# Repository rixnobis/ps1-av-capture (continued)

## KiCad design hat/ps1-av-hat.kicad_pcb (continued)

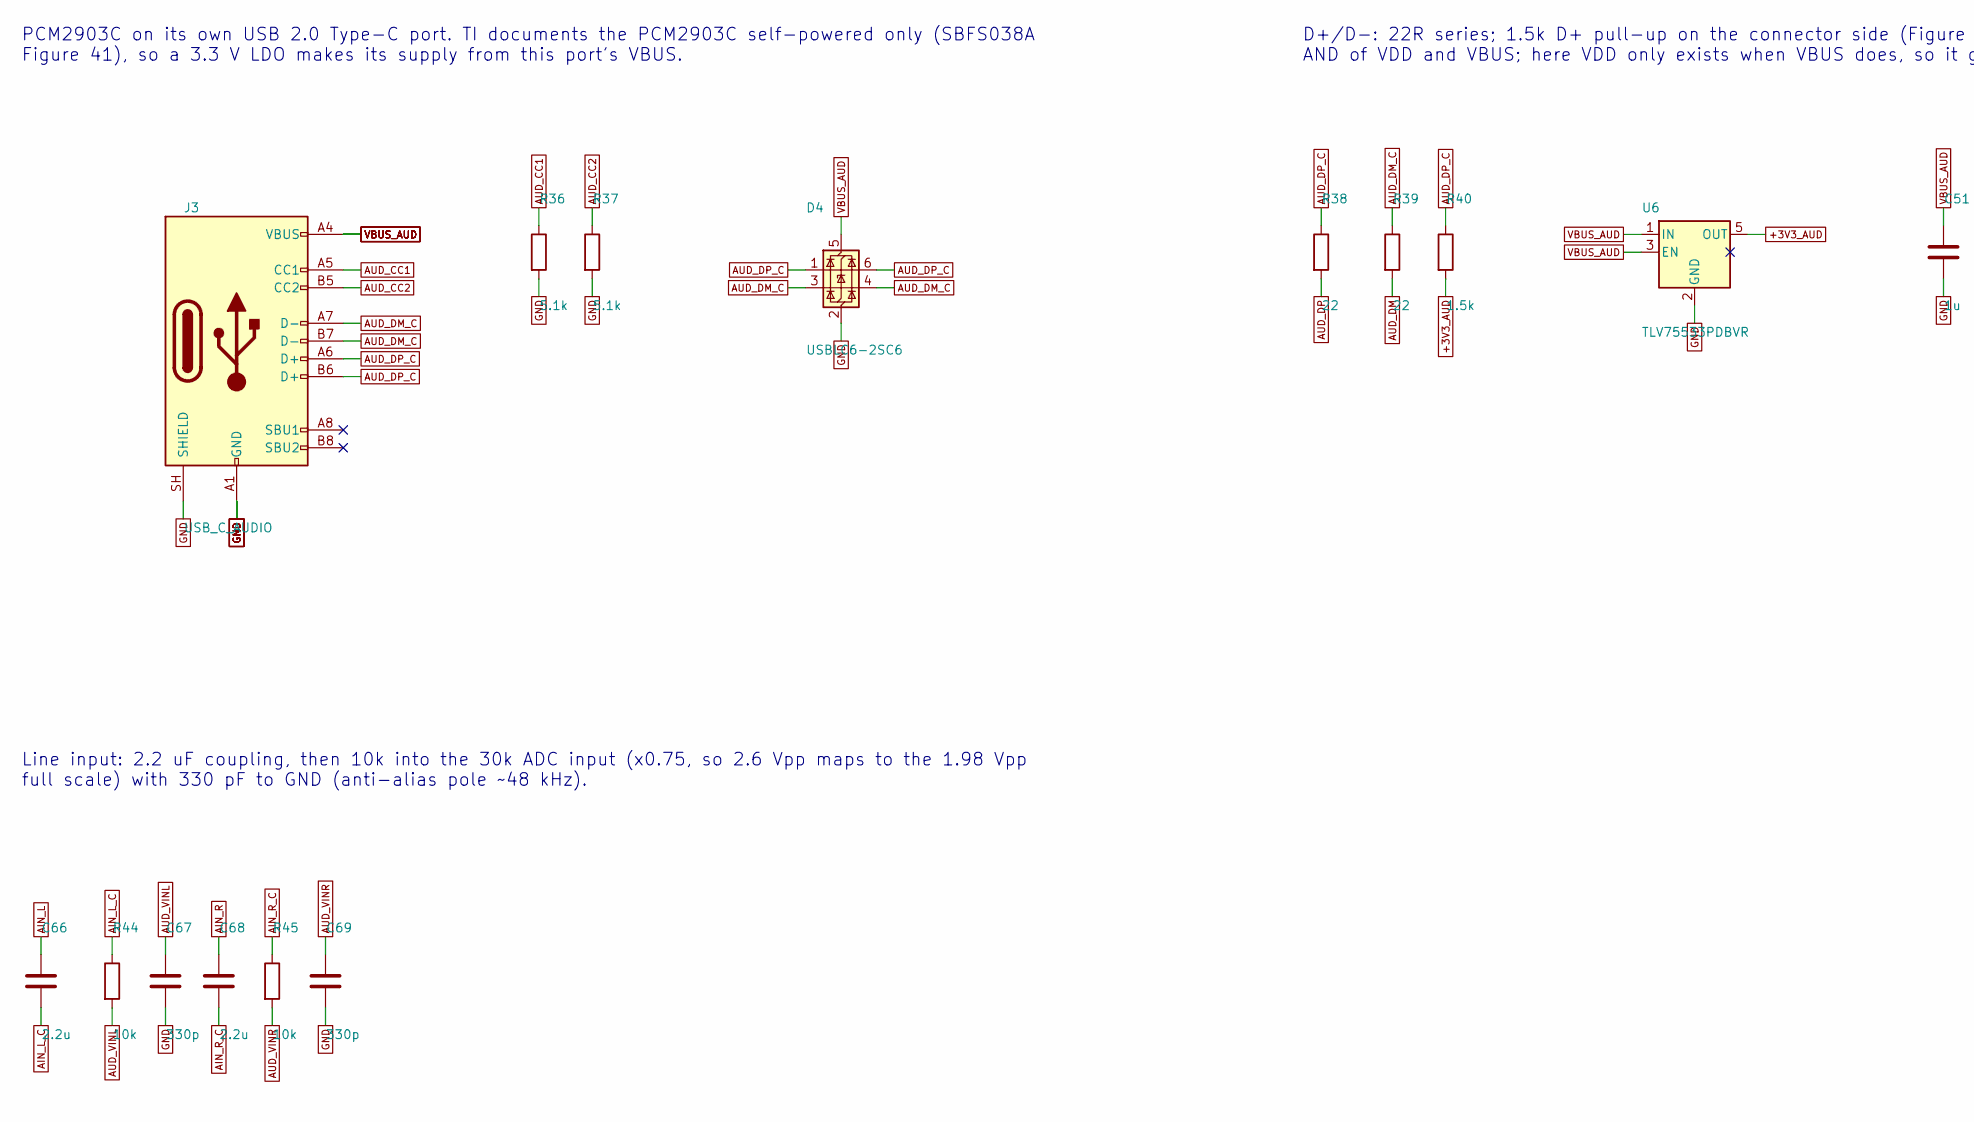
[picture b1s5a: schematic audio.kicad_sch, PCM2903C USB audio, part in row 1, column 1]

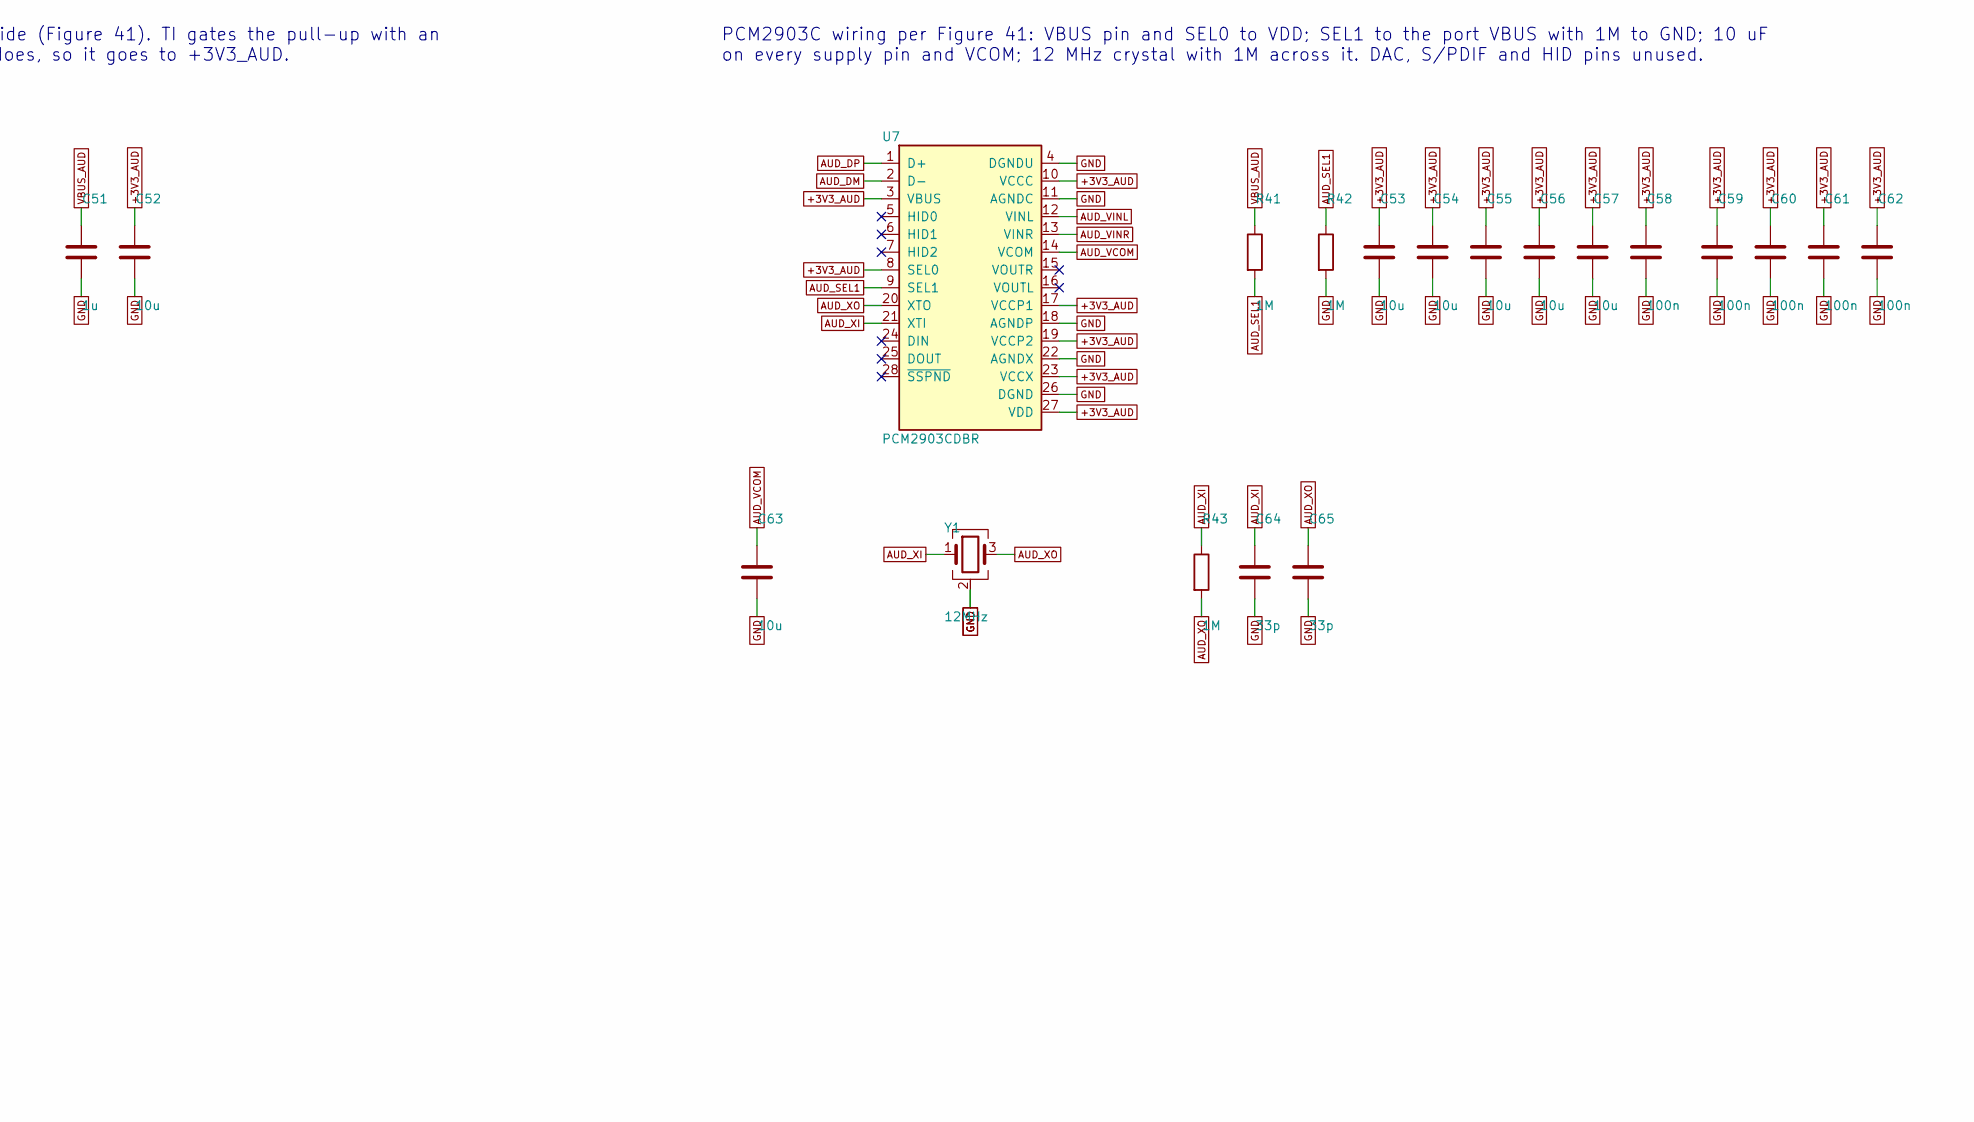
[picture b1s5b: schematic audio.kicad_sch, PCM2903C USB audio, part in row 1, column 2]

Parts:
C51: 1u; C_0402_1005Metric; LCSC C52923
C52, C53, C54, C55, C56, C57, C63: 10u; C_0603_1608Metric; LCSC C19702
C58, C59, C60, C61, C62: 100n; C_0402_1005Metric; LCSC C1525
C64, C65: 33p; C_0402_1005Metric; LCSC C1562
C66, C68: 2.2u; C_0603_1608Metric; LCSC C23630
C67, C69: 330p; C_0402_1005Metric; LCSC C13533
D4: USBLC6-2SC6; SOT-23-6; LCSC C7519
J3: USB_C_AUDIO; USB_C_Receptacle_HRO_TYPE-C-31-M-12; LCSC C165948
R36, R37: 5.1k; R_0402_1005Metric; LCSC C25905
R38, R39: 22; R_0402_1005Metric; LCSC C25092
R40: 1.5k; R_0402_1005Metric; LCSC C25867
R41, R42, R43: 1M; R_0402_1005Metric; LCSC C26083
R44, R45: 10k; R_0402_1005Metric; LCSC C25744
U6: TLV75533PDBVR; SOT-23-5; LCSC C404027
U7: PCM2903CDBR; SSOP-28_5.3x10.2mm_P0.65mm; LCSC C2861593
Y1: 12MHz; Crystal_SMD_3225-4Pin_3.2x2.5mm; LCSC C9002

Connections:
+3V3_AUD: C52.1, C53.1, C54.1, C55.1, C56.1, C57.1, C58.1, C59.1, C60.1, C61.1, C62.1, R40.2, U6.5 (OUT), U7.3 (VBUS), U7.8 (SEL0), U7.10 (VCCC), U7.17 (VCCP1), U7.19 (VCCP2), U7.23 (VCCX), U7.27 (VDD)
AIN_L: C66.1; also elsewhere on the board
AIN_L_C: C66.2, R44.1; also elsewhere on the board
AIN_R: C68.1; also elsewhere on the board
AIN_R_C: C68.2, R45.1; also elsewhere on the board
AUD_CC1: J3.A5 (CC1), R36.1
AUD_CC2: J3.B5 (CC2), R37.1
AUD_DM: R39.2, U7.2 (D-)
AUD_DM_C: D4.3 (I/O2), D4.4 (I/O2), J3.A7 (D-), J3.B7 (D-), R39.1
AUD_DP: R38.2, U7.1 (D+)
AUD_DP_C: D4.1 (I/O1), D4.6 (I/O1), J3.A6 (D+), J3.B6 (D+), R38.1, R40.1
AUD_SEL1: R41.2, R42.1, U7.9 (SEL1)
AUD_VCOM: C63.1, U7.14 (VCOM)
AUD_VINL: C67.1, R44.2, U7.12 (VINL)
AUD_VINR: C69.1, R45.2, U7.13 (VINR)
AUD_XI: C64.1, R43.1, U7.21 (XTI), Y1.1
AUD_XO: C65.1, R43.2, U7.20 (XTO), Y1.3
GND: C51.2, C52.2, C53.2, C54.2, C55.2, C56.2, C57.2, C58.2, C59.2, C60.2, C61.2, C62.2, C63.2, C64.2, C65.2, C67.2, C69.2, D4.2 (GND), J3.A1 (GND), J3.A12 (GND), J3.B1 (GND), J3.B12 (GND), J3.SH (SHIELD), R36.2, R37.2, R42.2, U6.2 (GND), U7.4 (DGNDU), U7.11 (AGNDC), U7.18 (AGNDP), U7.22 (AGNDX), U7.26 (DGND), Y1.2 (G), Y1.4 (G); also elsewhere on the board
VBUS_AUD: C51.1, D4.5 (VBUS), J3.A4 (VBUS), J3.A9 (VBUS), J3.B4 (VBUS), J3.B9 (VBUS), R41.1, U6.1 (IN), U6.3 (EN)

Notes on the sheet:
PCM2903C on its own USB 2.0 Type-C port. TI documents the PCM2903C self-powered only (SBFS038A Figure 41), so a 3.3 V LDO makes its supply from this port's VBUS.
D+/D-: 22R series; 1.5k D+ pull-up on the connector side (Figure 41). TI gates the pull-up with an AND of VDD and VBUS; here VDD only exists when VBUS does, so it goes to +3V3_AUD.
PCM2903C wiring per Figure 41: VBUS pin and SEL0 to VDD; SEL1 to the port VBUS with 1M to GND; 10 uF on every supply pin and VCOM; 12 MHz crystal with 1M across it. DAC, S/PDIF and HID pins unused.
Line input: 2.2 uF coupling, then 10k into the 30k ADC input (x0.75, so 2.6 Vpp maps to the 1.98 Vpp full scale) with 330 pF to GND (anti-alias pole ~48 kHz).

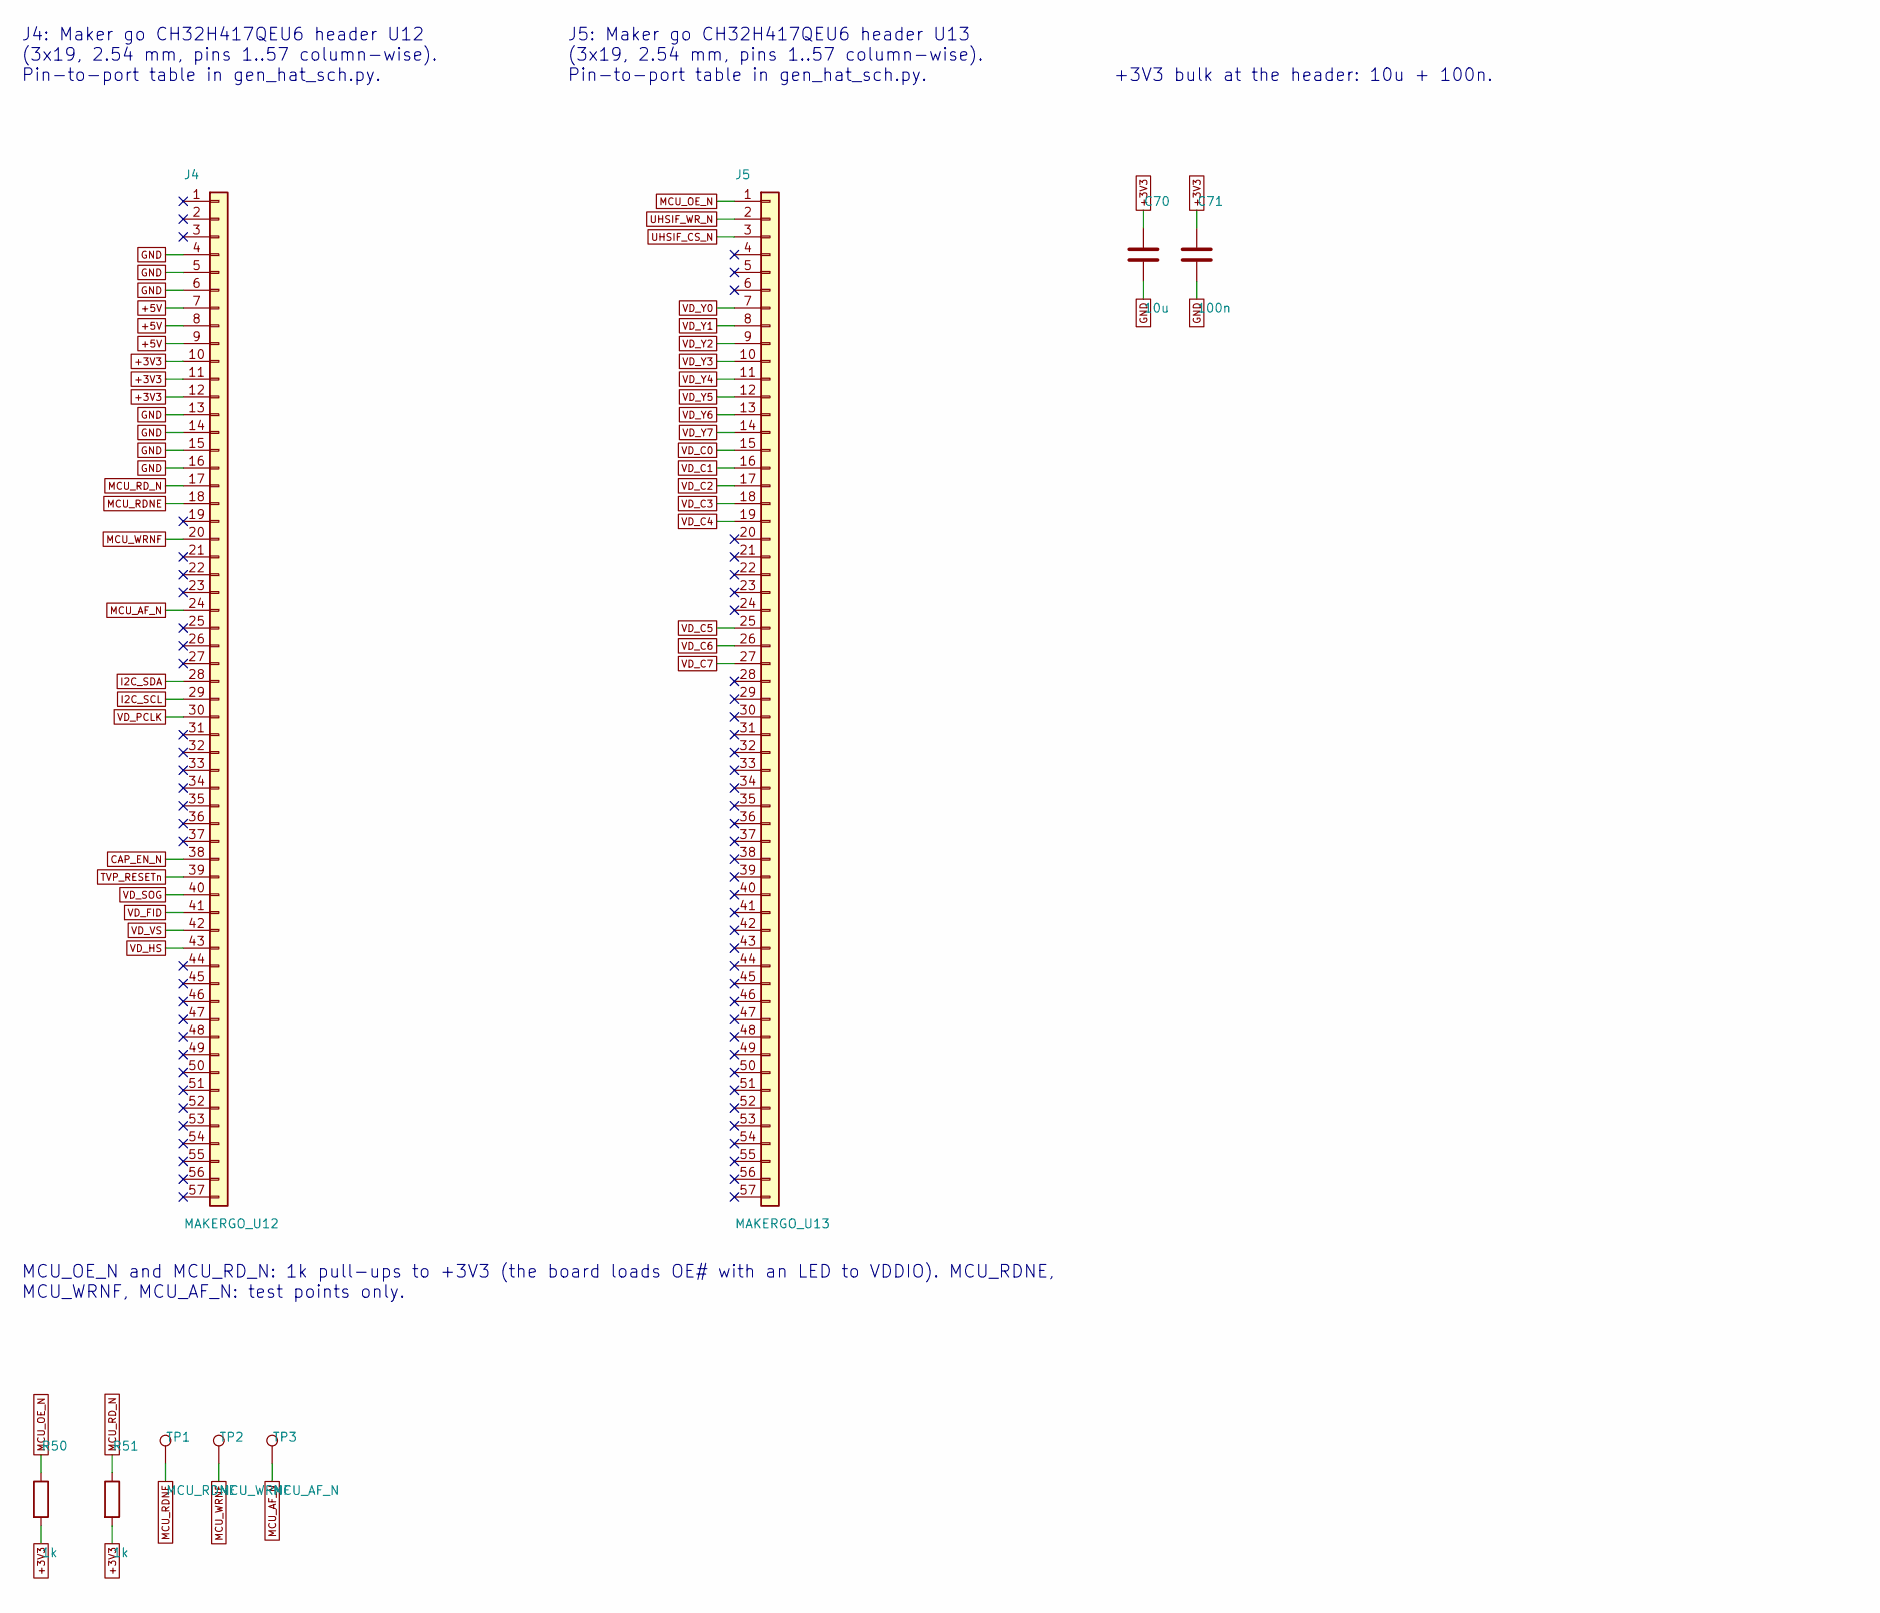
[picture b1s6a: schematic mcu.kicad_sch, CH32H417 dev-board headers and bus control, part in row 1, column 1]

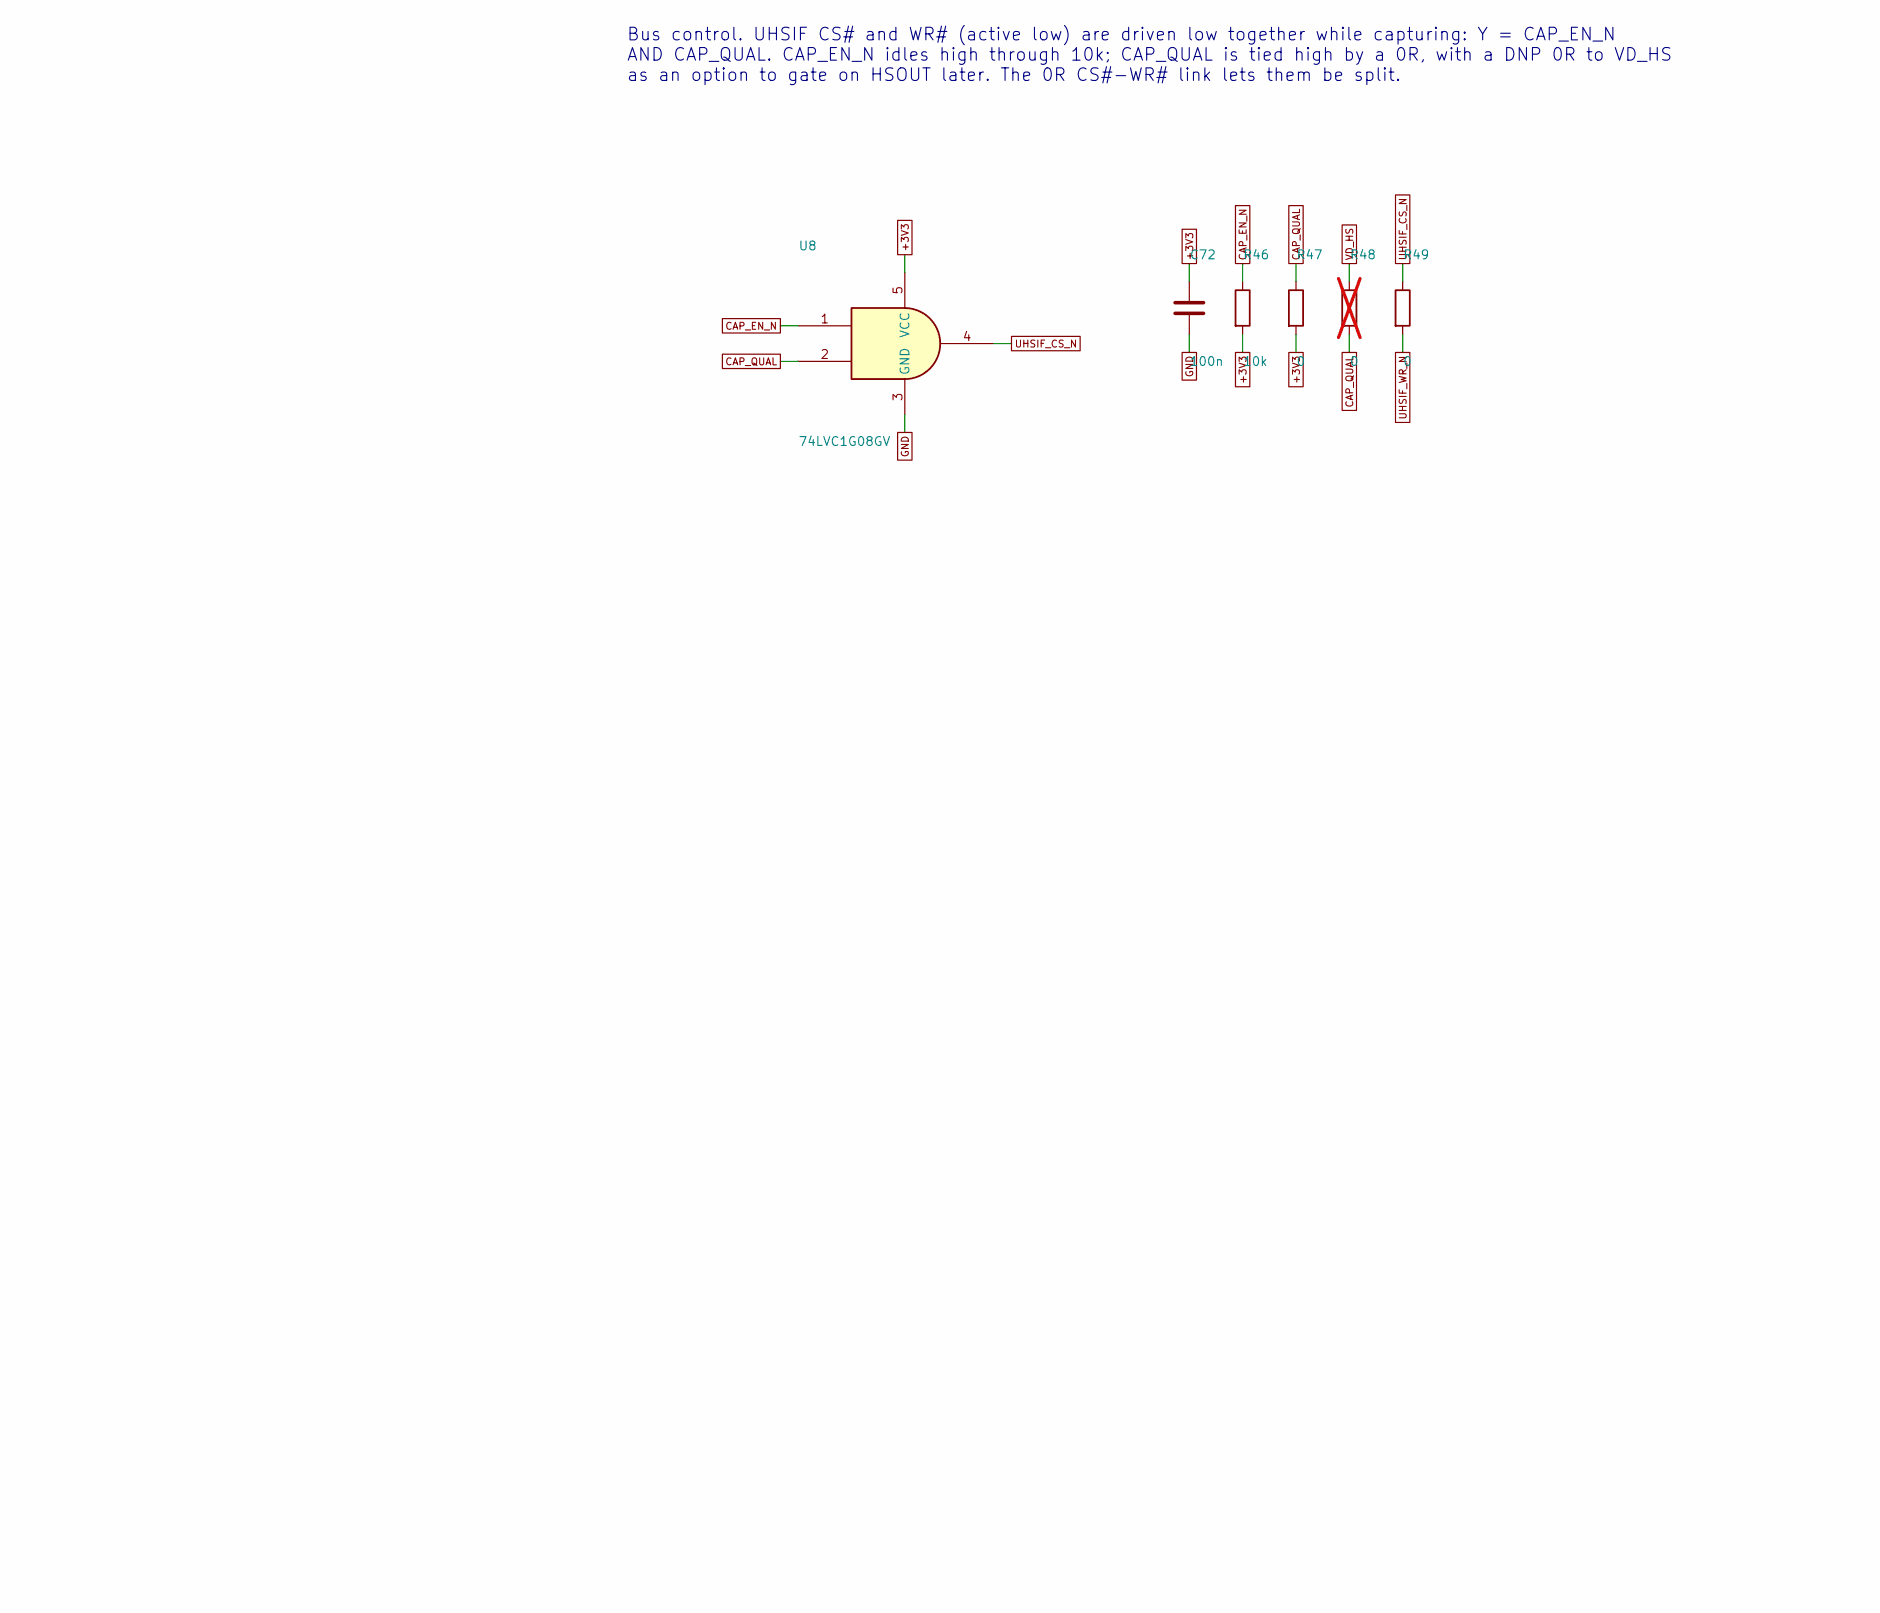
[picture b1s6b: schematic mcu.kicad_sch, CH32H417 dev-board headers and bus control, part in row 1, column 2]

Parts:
C70: 10u; C_0603_1608Metric; LCSC C19702
C71, C72: 100n; C_0402_1005Metric; LCSC C1525
J4: MAKERGO_U12; Socket_3x19_P2.54_MakerGo
J5: MAKERGO_U13; Socket_3x19_P2.54_MakerGo
R46: 10k; R_0402_1005Metric; LCSC C25744
R47, R49: 0; R_0402_1005Metric; LCSC C17168
R48: 0; R_0402_1005Metric; LCSC C17168; not fitted
R50, R51: 1k; R_0402_1005Metric; LCSC C11702
TP1: MCU_RDNE; TestPoint_Pad_D1.0mm
TP2: MCU_WRNF; TestPoint_Pad_D1.0mm
TP3: MCU_AF_N; TestPoint_Pad_D1.0mm
U8: 74LVC1G08GV; SOT-23-5; LCSC C19829591

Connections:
+3V3: C70.1, C71.1, C72.1, J4.10, J4.11, J4.12, R46.2, R47.2, R50.2, R51.2, U8.5 (VCC); also elsewhere on the board
+5V: J4.7, J4.8, J4.9; also elsewhere on the board
CAP_EN_N: J4.38, R46.1, U8.1
CAP_QUAL: R47.1, R48.2, U8.2
GND: C70.2, C71.2, C72.2, J4.4, J4.5, J4.6, J4.13, J4.14, J4.15, J4.16, U8.3 (GND); also elsewhere on the board
I2C_SCL: J4.29; also elsewhere on the board
I2C_SDA: J4.28; also elsewhere on the board
MCU_AF_N: J4.24, TP3.1
MCU_OE_N: J5.1, R50.1
MCU_RDNE: J4.18, TP1.1
MCU_RD_N: J4.17, R51.1
MCU_WRNF: J4.20, TP2.1
TVP_RESETn: J4.39; also elsewhere on the board
UHSIF_CS_N: J5.3, R49.1, U8.4
UHSIF_WR_N: J5.2, R49.2
VD_C0: J5.15; also elsewhere on the board
VD_C1: J5.16; also elsewhere on the board
VD_C2: J5.17; also elsewhere on the board
VD_C3: J5.18; also elsewhere on the board
VD_C4: J5.19; also elsewhere on the board
VD_C5: J5.25; also elsewhere on the board
VD_C6: J5.26; also elsewhere on the board
VD_C7: J5.27; also elsewhere on the board
VD_FID: J4.41; also elsewhere on the board
VD_HS: J4.43, R48.1; also elsewhere on the board
VD_PCLK: J4.30; also elsewhere on the board
VD_SOG: J4.40; also elsewhere on the board
VD_VS: J4.42; also elsewhere on the board
VD_Y0: J5.7; also elsewhere on the board
VD_Y1: J5.8; also elsewhere on the board
VD_Y2: J5.9; also elsewhere on the board
VD_Y3: J5.10; also elsewhere on the board
VD_Y4: J5.11; also elsewhere on the board
VD_Y5: J5.12; also elsewhere on the board
VD_Y6: J5.13; also elsewhere on the board
VD_Y7: J5.14; also elsewhere on the board

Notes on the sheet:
J4: Maker go CH32H417QEU6 header U12 (3x19, 2.54 mm, pins 1..57 column-wise). Pin-to-port table in gen_hat_sch.py.
J5: Maker go CH32H417QEU6 header U13 (3x19, 2.54 mm, pins 1..57 column-wise). Pin-to-port table in gen_hat_sch.py.
+3V3 bulk at the header: 10u + 100n.
Bus control. UHSIF CS# and WR# (active low) are driven low together while capturing: Y = CAP_EN_N AND CAP_QUAL. CAP_EN_N idles high through 10k; CAP_QUAL is tied high by a 0R, with a DNP 0R to VD_HS as an option to gate on HSOUT later. The 0R CS#-WR# link lets them be split.
MCU_OE_N and MCU_RD_N: 1k pull-ups to +3V3 (the board loads OE# with an LED to VDDIO). MCU_RDNE, MCU_WRNF, MCU_AF_N: test points only.

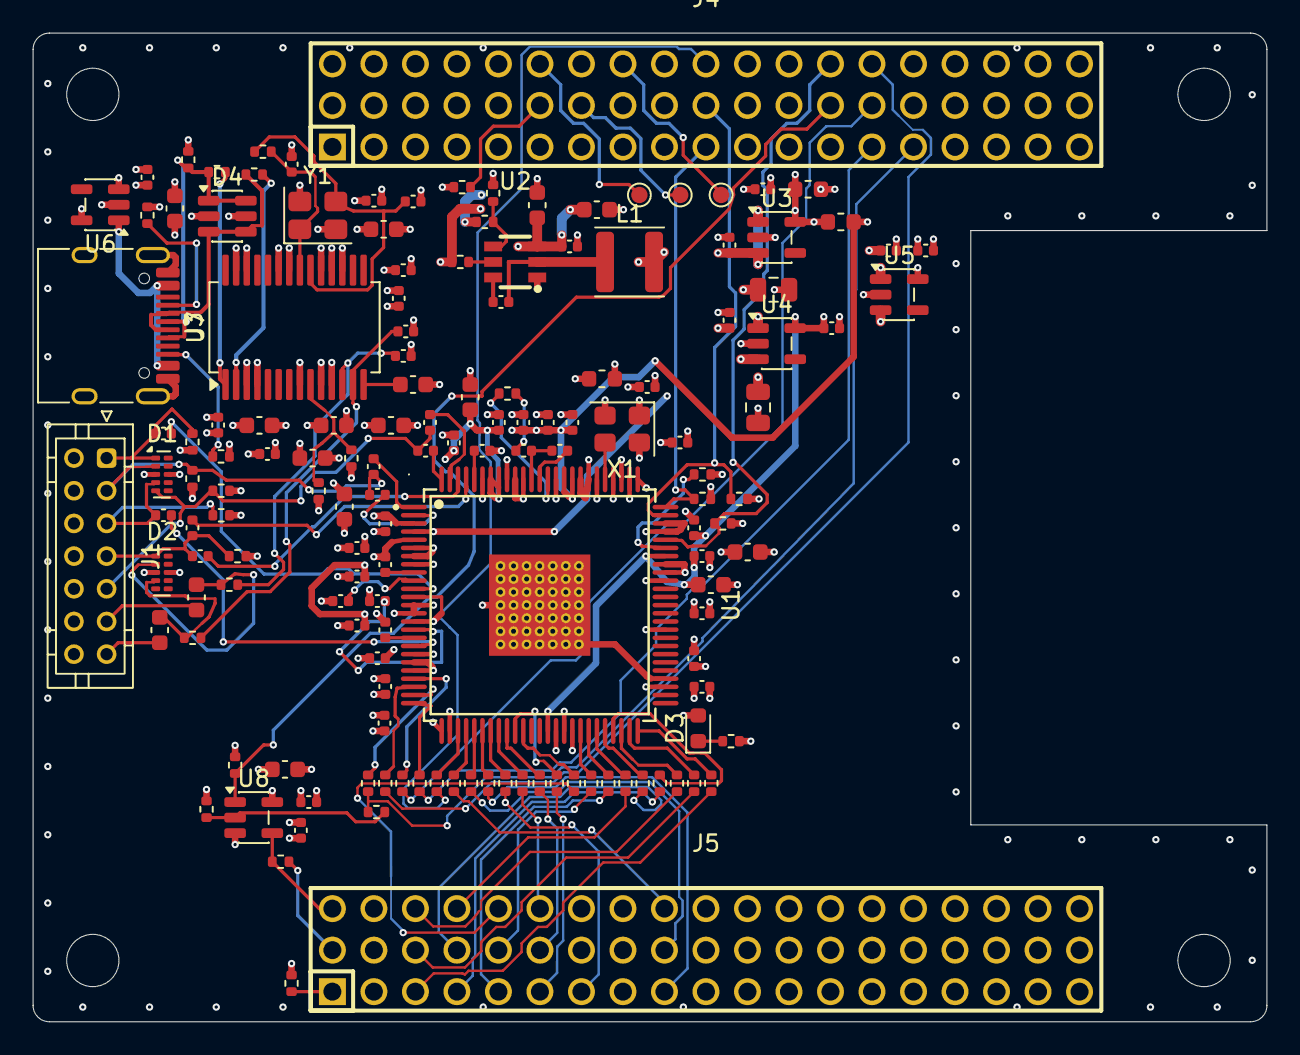
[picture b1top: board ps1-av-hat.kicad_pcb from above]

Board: 4 copper layers, 75.5 x 60.5 mm, 152 parts (0 on the bottom side), 111 nets.

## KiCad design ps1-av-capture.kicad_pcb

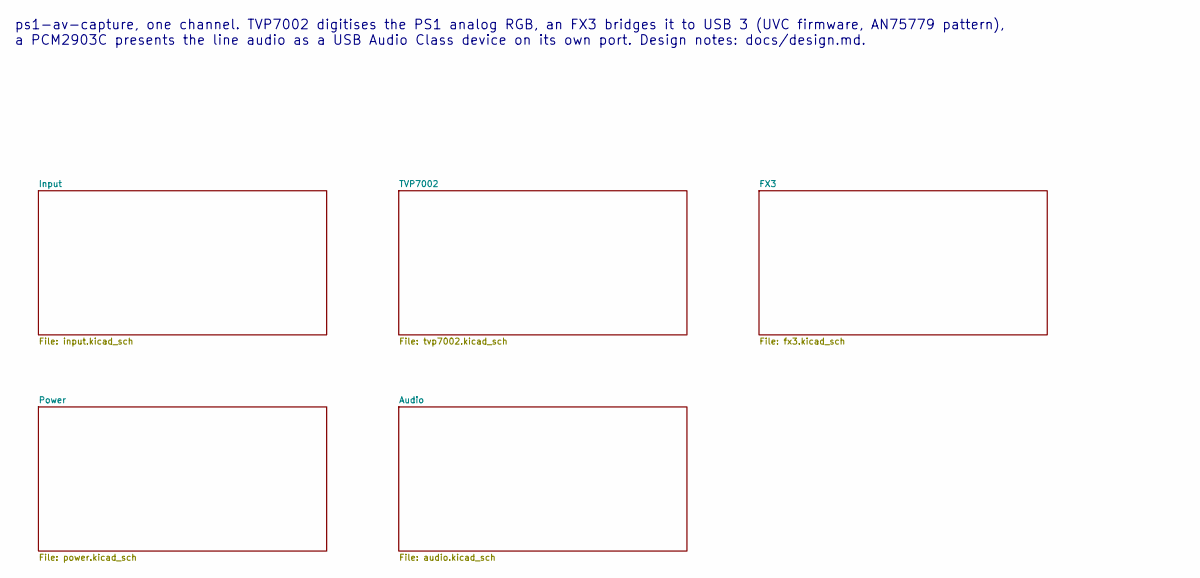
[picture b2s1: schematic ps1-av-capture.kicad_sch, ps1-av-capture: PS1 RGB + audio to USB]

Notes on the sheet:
ps1-av-capture, one channel. TVP7002 digitises the PS1 analog RGB, an FX3 bridges it to USB 3 (UVC firmware, AN75779 pattern), a PCM2903C presents the line audio as a USB Audio Class device on its own port. Design notes: docs/design.md.

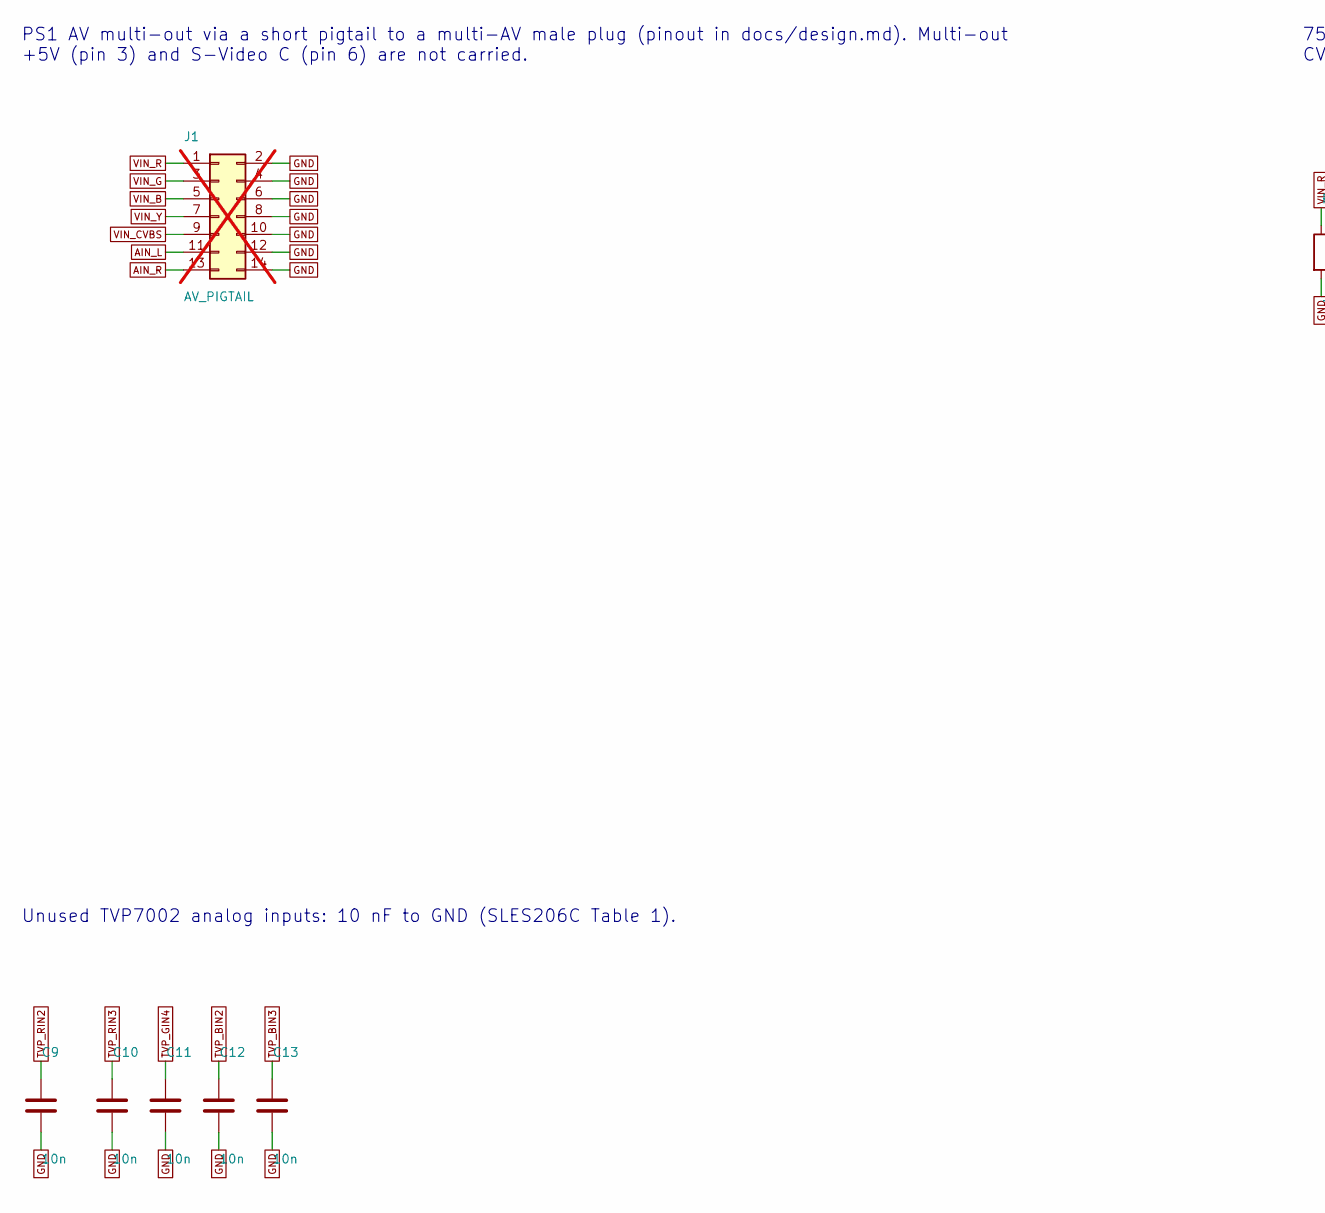
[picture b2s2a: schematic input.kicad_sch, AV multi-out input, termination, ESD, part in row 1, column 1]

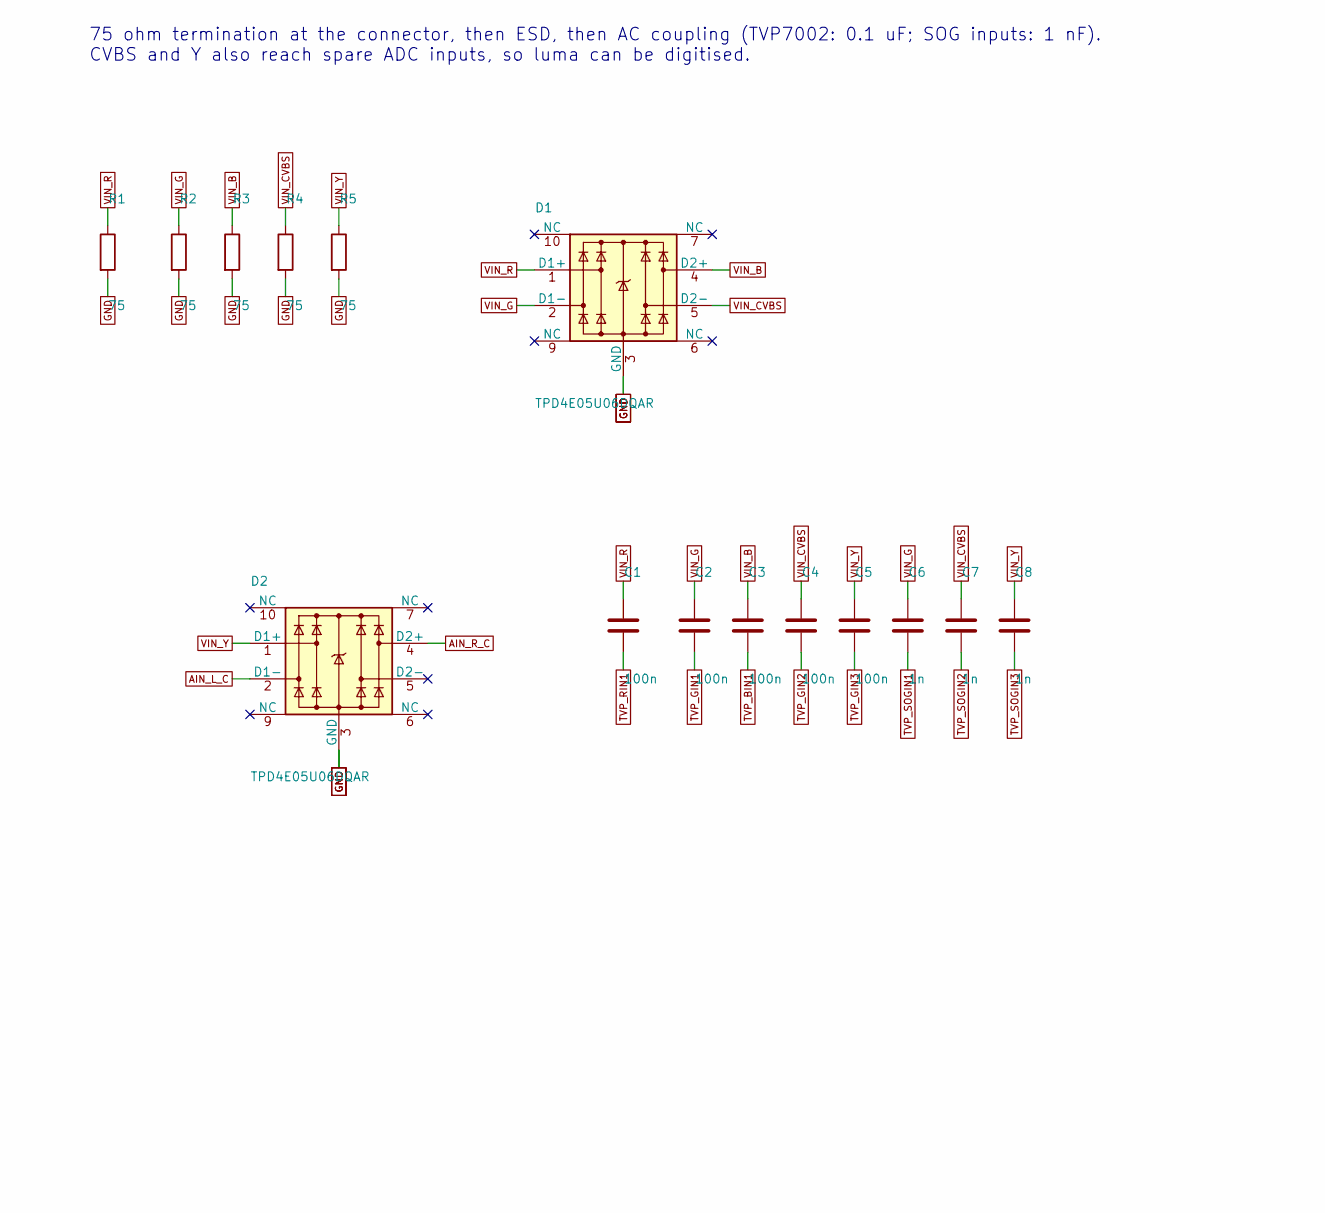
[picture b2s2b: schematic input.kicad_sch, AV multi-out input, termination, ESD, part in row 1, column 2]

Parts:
C1, C2, C3, C4, C5: 100n; C_0402_1005Metric; LCSC C1525
C6, C7, C8: 1n; C_0402_1005Metric; LCSC C1523
C9, C10, C11, C12, C13: 10n; C_0402_1005Metric; LCSC C15195
D1, D2: TPD4E05U06DQAR; USON-10_2.5x1.0mm_P0.5mm; LCSC C138714
J1: AV_PIGTAIL; JST_PHD_B14B-PHDSS_2x07_P2.00mm_Vertical; LCSC C471471; not fitted
R1, R2, R3, R4, R5: 75; R_0402_1005Metric; LCSC C25133

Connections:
AIN_L: J1.11; also elsewhere on the board
AIN_L_C: D2.2 (D1-); also elsewhere on the board
AIN_R: J1.13; also elsewhere on the board
AIN_R_C: D2.4 (D2+); also elsewhere on the board
GND: C9.2, C10.2, C11.2, C12.2, C13.2, D1.3 (GND), D1.8 (GND), D2.3 (GND), D2.8 (GND), J1.2, J1.4, J1.6, J1.8, J1.10, J1.12, J1.14, R1.2, R2.2, R3.2, R4.2, R5.2; also elsewhere on the board
TVP_BIN1: C3.2; also elsewhere on the board
TVP_BIN2: C12.1; also elsewhere on the board
TVP_BIN3: C13.1; also elsewhere on the board
TVP_GIN1: C2.2; also elsewhere on the board
TVP_GIN2: C4.2; also elsewhere on the board
TVP_GIN3: C5.2; also elsewhere on the board
TVP_GIN4: C11.1; also elsewhere on the board
TVP_RIN1: C1.2; also elsewhere on the board
TVP_RIN2: C9.1; also elsewhere on the board
TVP_RIN3: C10.1; also elsewhere on the board
TVP_SOGIN1: C6.2; also elsewhere on the board
TVP_SOGIN2: C7.2; also elsewhere on the board
TVP_SOGIN3: C8.2; also elsewhere on the board
VIN_B: C3.1, D1.4 (D2+), J1.5, R3.1
VIN_CVBS: C4.1, C7.1, D1.5 (D2-), J1.9, R4.1
VIN_G: C2.1, C6.1, D1.2 (D1-), J1.3, R2.1
VIN_R: C1.1, D1.1 (D1+), J1.1, R1.1
VIN_Y: C5.1, C8.1, D2.1 (D1+), J1.7, R5.1

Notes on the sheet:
PS1 AV multi-out via a short pigtail to a multi-AV male plug (pinout in docs/design.md). Multi-out +5V (pin 3) and S-Video C (pin 6) are not carried.
75 ohm termination at the connector, then ESD, then AC coupling (TVP7002: 0.1 uF; SOG inputs: 1 nF). CVBS and Y also reach spare ADC inputs, so luma can be digitised.
Unused TVP7002 analog inputs: 10 nF to GND (SLES206C Table 1).
